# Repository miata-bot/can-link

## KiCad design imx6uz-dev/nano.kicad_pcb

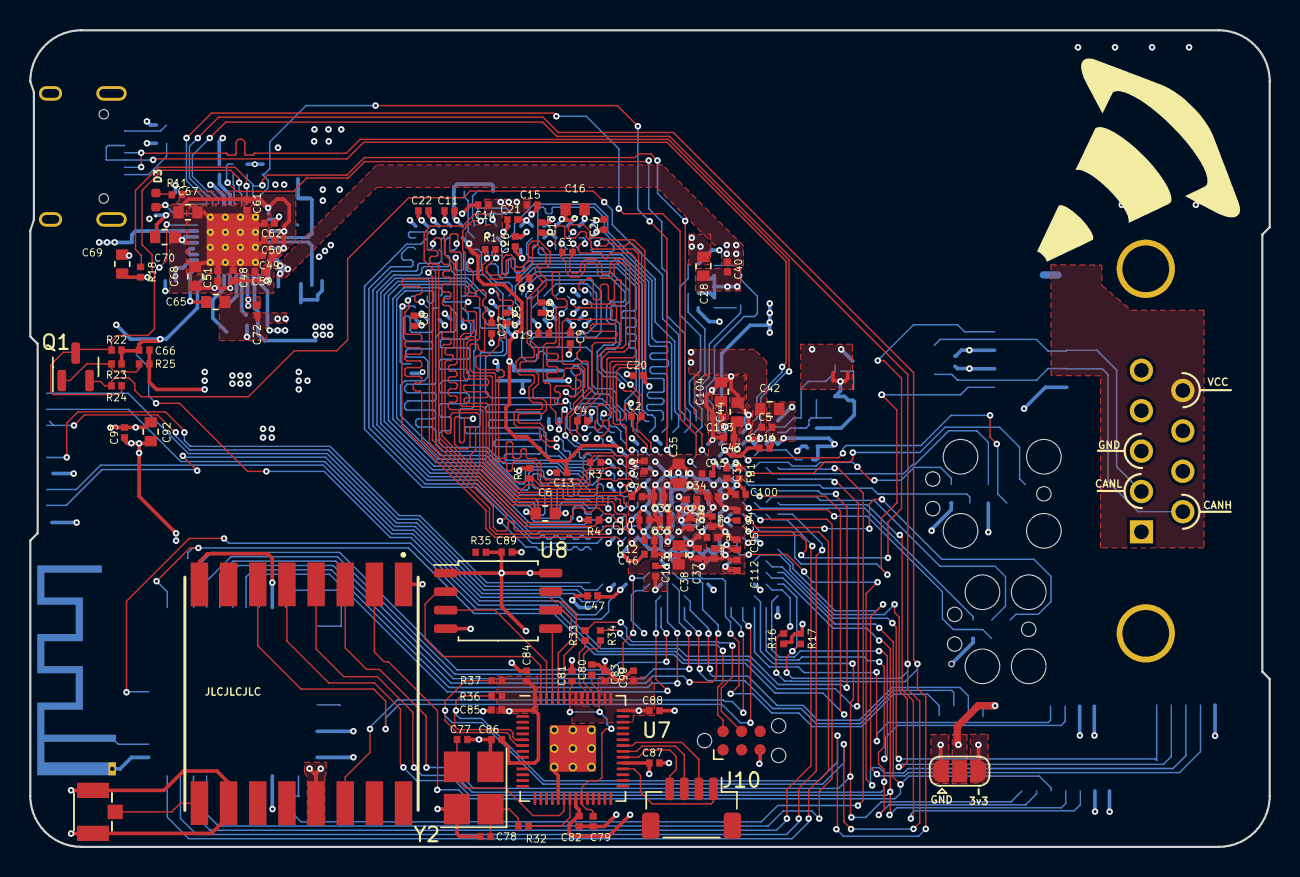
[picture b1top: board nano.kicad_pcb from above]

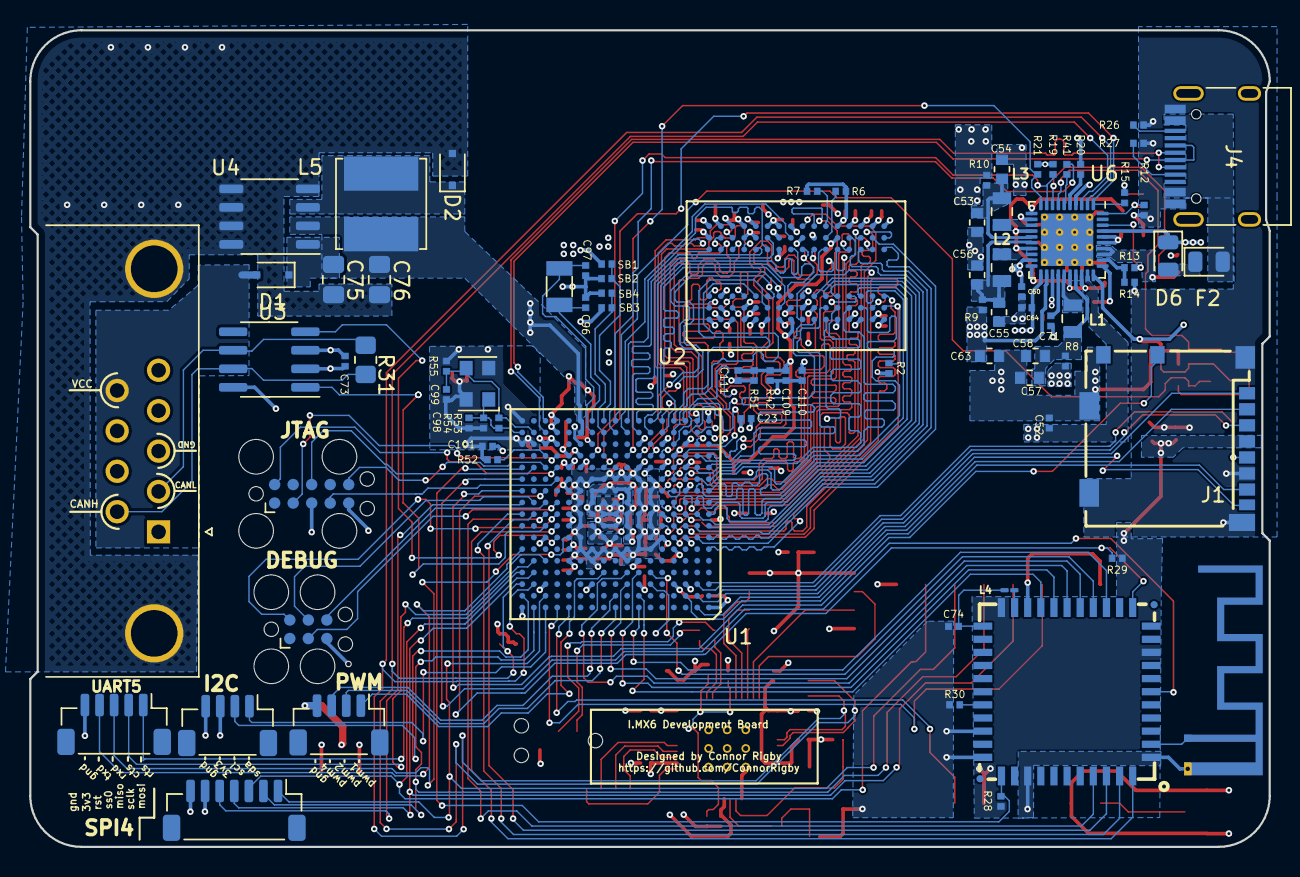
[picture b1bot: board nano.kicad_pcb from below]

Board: 4 copper layers, 85.0 x 56.0 mm, 195 parts (81 on the bottom side), 188 nets.

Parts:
AE1: U.FL-R-SMT-1(10); HRS_U.FL-R-SMT-1(10)
ANT1: PCB_ANTENNA; Texas_SWRA117D_2.4GHz_Left
C1, C2, C3, C4: 2.2pF; C_0402_narrow
C5, C7, C8, C9, C10, C11, C12, C13, C14, C15, C17, C18, C19, C20, C21, C22, C23, C24, C25, C26, C27, C30, C31, C32, C33, C34, C36, C37, C40, C41, C43, C45, C46, C47, C73, C94, C95, C102, C114: 0.22uF; C_0402_narrow
C6, C42, C44, C53, C54, C55, C56, C57, C58, C104: 10uF; C_0603_narrow
C16, C28, C35, C38, C92: 22uF; C_0603_narrow
C29, C39, C48, C49, C50, C52, C60, C62, C110: 4.7uF; C_0402_narrow
C51, C59, C61, C64, C71, C72, C79, C81, C89, C101: 1uF; C_0402_narrow
C63: 1uF; C_0603_narrow
C65: 0.1uF; C_0603_narrow
C66: 0.47uF; C_0402_narrow
C67, C68: 100uF; C_0603_narrow
C69, C70: 4.7uF; C_0603_narrow
C74: 4.7F; C_0402_narrow
C75, C76: 10uF; C_0805_2012Metric_Pad1.18x1.45mm_HandSolder
C77, C78: 10pF; C_0402_narrow
C80, C82, C83, C84, C85, C86, C87, C88, C90, C93, C100, C103, C109, C111, C112, C113: 0.1uF; C_0402_narrow
C96, C97, C98, C99: 18pF; C_0402_narrow
D1, D2: D_Small; D_SOD-323F
D3: LED; LED_0402_1005Metric
D6: D_Schottky; D_0805_2012Metric
F2: Polyfuse; D_0805_2012Metric
FB1: Bead; R_0402_narrow
J1: SD-104031; uSD_104031
J2: TAG_CONNECT_JTAG; Tag-Connect_TC2050-IDC-FP_2x05_P1.27mm_Vertical
J3: TC2030-IDC; Tag-Connect_TC2030-IDC-FP_2x03_P1.27mm_Vertical
J4: USB_C_Receptacle_USB2.0; USB_C_Receptacle_HRO_TYPE-C-31-M-12
J5: CAN; DSUB-9_Female_Horizontal_P2.77x2.84mm_EdgePinOffset4.94mm_H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
J6: UART5; JST_SH_BM05B-SRSS-TB_1x05-1MP_P1.00mm_Vertical
J7: I2C4; JST_SH_BM04B-SRSS-TB_1x04-1MP_P1.00mm_Vertical
J8: ECSPI4; JST_SH_BM07B-SRSS-TB_1x07-1MP_P1.00mm_Vertical
J9: PWM; JST_SH_BM04B-SRSS-TB_1x04-1MP_P1.00mm_Vertical
J10: TC2030-IDC; Tag-Connect_TC2030-IDC-NL_2x03_P1.27mm_Vertical
J11: Conn_01x05; JST_SH_BM04B-SRSS-TB_1x04-1MP_P1.00mm_Vertical
JP1: IO_SW; SolderJumper-3_P1.3mm_Open_RoundedPad1.0x1.5mm
L1, L2, L3: 1uH; L_0805_narrow
L4: 3.3uH; L_01005_0402Metric_Pad0.57x0.30mm_HandSolder
L5: 6.8uH; L_Bourns_SRN6045TA
MOD1: RTL8723BS; RL-SM02BD(RTL8723BS)
Q1: 2SK3018; SOT-23
R1: 470; R_0402_narrow
R2, R4, R5: 10K; R_0402_narrow
R3, R6, R7: 240; R_0402_narrow
R8, R9, R10: 0.02; R_0402_narrow
R11: 47; R_0402_narrow
R12, R14, R24: DNP; R_0402_narrow
R13, R16, R17, R52: 4.7K; R_0402_narrow
R15, R18, R19, R21, R22, R23, R25: 100K; R_0402_narrow
R20, R41: 0R; R_0402_narrow
R26, R27: 5.1k; R_0402_narrow
R28, R29, R32, R35, R36, R37: 1k; R_0402_narrow
R30: 7.13; R_0402_narrow
R31: 120; R_0805_2012Metric_Pad1.20x1.40mm_HandSolder
R33, R34: 27.4; R_0402_narrow
R42, R51: 1.5K; R_0402_narrow
R53: 1M; R_0402_narrow
R54: 499; R_0402_narrow
R55: 2.2M; R_0402_narrow
SB1, SB2, SB3, SB4: 4.7K; R_0402_narrow
U1: IMX6UL_BGA289
U2: DDR3_BGA96
U3: TJA1051T; SOIC-8_3.9x4.9mm_P1.27mm
U4: AP1509; SOP-8_3.9x4.9mm_P1.27mm
U5: RFM69HCW; XCVR_RFM69HW
U6: PF1550; QFN-40-1EP_5x5mm_P0.4mm_EP3.6x3.6mm_ThermalVias
U7: RP2040; RP2040-QFN-56
U8: W25Q128JVS; SOIC-8_5.23x5.23mm_P1.27mm
XTAL2: 24MHz 50ppm; Oscillator_SMD_EuroQuartz_XO32-4Pin_3.2x2.5mm
Y1: 32.768 kHz; Crystal_SMD_3215-2Pin_3.2x1.5mm
Y2: 12mhz; Crystal_SMD_3225-4Pin_3.2x2.5mm_HandSoldering

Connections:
5V: C76.1, D6.1 (K), L5.2, U1.T12 (USB_OTG1_VBUS), U1.U12 (USB_OTG2_VBUS), U4.2 (VOUT), U6.37 (VBUSIN(VIN))
/Clock_and_Control/BOOT0: SB3.1, SB4.1, U1.T10 (BOOT_MODE0)
/Clock_and_Control/BOOT1: SB1.1, SB2.1, U1.U10 (BOOT_MODE1)
/Clock_and_Control/IMX_XTALI: C99.1, R53.1, R55.1, U1.T16 (XTALI), XTAL2.3
/Clock_and_Control/IMX_XTALO: C98.1, R53.2, R54.1, U1.T17 (XTALO), XTAL2.1
/Clock_and_Control/JTAG_MOD: R52.2, U1.P15 (JTAG_MOD)
/Clock_and_Control/JTAG_TCK: J2.4 (SWDCLK/TCK), U1.M14 (JTAG_TCK)
/Clock_and_Control/JTAG_TDI: J2.8 (NC/TDI), U1.N16 (JTAG_TDI)
/Clock_and_Control/JTAG_TDO: J2.6 (SWO/TDO), U1.N15 (JTAG_TDO)
/Clock_and_Control/JTAG_TMS: J2.2 (SWDIO/TMS), U1.P14 (JTAG_TMS)
/Clock_and_Control/JTAG_TRST_B: J2.10 (~RESET), U1.N14 (JTAG_TRST_B)
/Clock_and_Control/RTC_XTALI: C97.1, U1.T11 (RTC_XTALI), Y1.2
/Clock_and_Control/RTC_XTALO: C96.1, U1.U11 (RTC_XTALO), Y1.1
/Clock_and_Control/VDDA_ADC: C100.1, C101.1, FB1.2, U1.L13 (VDDA_ADC_3P3), U1.M13 (ADC_VREFH)
/DDR/A0: U1.L5 (DRAM_ADDR00), U2.N3 (A0)
/DDR/A1: U1.H2 (DRAM_ADDR01), U2.P7 (A1)
/DDR/A2: U1.K1 (DRAM_ADDR02), U2.P3 (A2)
/DDR/A3: U1.M2 (DRAM_ADDR03), U2.N2 (A3)
/DDR/A4: U1.K4 (DRAM_ADDR04), U2.P8 (A4)
/DDR/A5: U1.L1 (DRAM_ADDR05), U2.P2 (A5)
/DDR/A6: U1.G2 (DRAM_ADDR06), U2.R8 (A6)
/DDR/A7: U1.H4 (DRAM_ADDR07), U2.R2 (A7)
/DDR/A8: U1.J4 (DRAM_ADDR08), U2.T8 (A8)
/DDR/A9: U1.L2 (DRAM_ADDR09), U2.R3 (A9)
/DDR/A10: U1.M4 (DRAM_ADDR10), U2.L7 (A10_AP)
/DDR/A11: U1.K3 (DRAM_ADDR11), U2.R7 (A11)
/DDR/A12: U1.L4 (DRAM_ADDR12), U2.N7 (A12_BC#)
/DDR/A13: U1.H3 (DRAM_ADDR13), U2.T3 (A13)
/DDR/A14: U1.G1 (DRAM_ADDR14), U2.T7 (A14)
/DDR/A15: U1.K5 (DRAM_ADDR15), U2.M7 (A15)
/DDR/BA0: U1.M1 (DRAM_SDBA0), U2.M2 (BA0)
/DDR/BA1: U1.H1 (DRAM_SDBA1), U2.N8 (BA1)
/DDR/BA2: U1.K2 (DRAM_SDBA2), U2.M3 (BA2)
/DDR/CAS#: U1.J2 (DRAM_CAS_B), U2.K3 (CAS#)
/DDR/CK+: R1.2, U1.P1 (DRAM_SDCLK0_P), U2.J7 (CK)
/DDR/CK-: R1.1, U1.P2 (DRAM_SDCLK0_N), U2.K7 (CK#)
/DDR/CKE0: R5.1, U1.M3 (DRAM_SDCKE0), U2.K9 (CKE)
/DDR/CKE1: R4.1, U1.J3 (DRAM_SDCKE1), U2.J9 (CKE1)
/DDR/CS0#: U1.N2 (DRAM_CS0_B), U2.L2 (CS#)
/DDR/CS1#: U1.H5 (DRAM_CS1_B), U2.L1 (CS1)
/DDR/DML: U1.T7 (DRAM_DQM0), U2.E7 (DML)
/DDR/DMU: U1.T3 (DRAM_DQM1), U2.D3 (DMU)
/DDR/DQL0: U1.T4 (DRAM_DATA00), U2.E3 (DQL0)
/DDR/DQL1: U1.U6 (DRAM_DATA01), U2.H3 (DQL4)
/DDR/DQL2: U1.T6 (DRAM_DATA02), U2.H7 (DQL7)
/DDR/DQL3: U1.U7 (DRAM_DATA03), U2.F8 (DQL3)
/DDR/DQL4: U1.U8 (DRAM_DATA04), U2.F7 (DQL1)
/DDR/DQL5: U1.T8 (DRAM_DATA05), U2.H8 (DQL5)
/DDR/DQL6: U1.T5 (DRAM_DATA06), U2.G2 (DQL6)
/DDR/DQL7: U1.U4 (DRAM_DATA07), U2.F2 (DQL2)
/DDR/DQSL+: C1.1, C2.1, U1.P6 (DRAM_SDQS0_P), U2.F3 (DQSL)
/DDR/DQSL-: C1.2, C2.2, U1.P7 (DRAM_SDQS0_N), U2.G3 (DQSL#)
/DDR/DQSU+: C3.1, C4.1, U1.T1 (DRAM_SDQS1_P), U2.C7 (DQSU)
/DDR/DQSU-: C3.2, C4.2, U1.T2 (DRAM_SDQS1_N), U2.B7 (DQSU#)
/DDR/DQU0: U1.U2 (DRAM_DATA08), U2.D7 (DQU0)
/DDR/DQU1: U1.U3 (DRAM_DATA09), U2.C3 (DQU1)
/DDR/DQU2: U1.U5 (DRAM_DATA10), U2.C8 (DQU2)
/DDR/DQU3: U1.R4 (DRAM_DATA11), U2.C2 (DQU3)
/DDR/DQU4: U1.P5 (DRAM_DATA12), U2.A7 (DQU4)
/DDR/DQU5: U1.P3 (DRAM_DATA13), U2.A2 (DQU5)
/DDR/DQU6: U1.R2 (DRAM_DATA14), U2.B8 (DQU6)
/DDR/DQU7: U1.R1 (DRAM_DATA15), U2.A3 (DQU7)
/DDR/ODT0: U1.N1 (DRAM_ODT0), U2.K1 (ODT)
/DDR/ODT1: U1.F1 (DRAM_ODT1), U2.J1 (ODT1)
/DDR/RAS#: U1.M5 (DRAM_RAS_B), U2.J3 (RAS#)
/DDR/RESET#: R2.1, U1.G4 (DRAM_RESET), U2.T2 (RESET#)
/DDR/WE#: U1.J1 (DRAM_SDWE_B), U2.L3 (WE#)
/DDR/ZQ: R6.2, U2.L8 (ZQ)
/DDR/ZQ1: R7.2, U2.L9 (ZQ1)
/DDR/ZQPAD: R3.2, U1.N4 (DRAM_ZQPAD)
/IMX_Peripherals_1/TOUCH_MISO: J8.3, U1.D17 (ENET2_TX_CLK), U5.2 (MISO)
/IMX_Peripherals_1/TOUCH_MOSI: J8.1, U1.B15 (ENET2_TX_EN), U5.3 (MOSI)
/IMX_Peripherals_1/TOUCH_SCL: J7.2, U1.B17 (ENET2_RX_EN)
/IMX_Peripherals_1/TOUCH_SCLK: J8.2, U1.A16 (ENET2_TX_DATA1), U5.4 (SCK)
/IMX_Peripherals_1/TOUCH_SDA: J7.1, U1.A15 (ENET2_TX_DATA0)
/IMX_Peripherals_1/TOUCH_SS0: J8.4, U1.D16 (ENET2_RX_ER), U5.5 (NSS)
/IMX_Peripherals_2/CC1: J4.A5 (CC1), R27.1
/IMX_Peripherals_2/CC2: J4.B5 (CC2), R26.1
/IMX_Peripherals_2/LCD_D0: J9.3, U1.B9 (LCD_DATA00)
/IMX_Peripherals_2/LCD_D1: J9.2, U1.A9 (LCD_DATA01)
/IMX_Peripherals_2/LCD_D3: J9.1, U1.D10 (LCD_DATA03)
/IMX_Peripherals_2/VDDUSB_CAP: C103.1, C104.1, U1.R12 (VDD_USB_CAP)
/IMX_Power_Pins/VDD_SNVS_CAP: C45.1, U1.N12 (VDD_SNVS_CAP)
/PMIC PF1550/BUCK_VIN: C75.1, D1.1 (K), U4.1 (VIN)
/PMIC PF1550/CHGB: D3.1 (K), R12.1, U6.40 ((GND)CHGB)
/PMIC PF1550/ON_KEY: R18.1, U6.8 (ONKEY)
/PMIC PF1550/POWERON: R41.1, U6.6 (POWERON)
/PMIC PF1550/STANDBY: Q1.3 (D), R22.2, R24.1, U6.7 (STANDBY)
/PMIC PF1550/SW1LX: L1.2, U6.25 (SW1LX)
/PMIC PF1550/SW1OUT: C57.1, C58.1, L1.1, R8.1, U6.27 (SW1FB)
/PMIC PF1550/SW2LX: L2.2, U6.18 (SW2LX)
/PMIC PF1550/SW2OUT: C55.1, C56.1, L2.1, R9.1, U6.16 (SW2FB)
/PMIC PF1550/SW3LX: L3.2, U6.13 (SW3LX)
/PMIC PF1550/SW3OUT: C53.1, C54.1, L3.1, R10.1, U6.15 (SW3FB)
/PMIC PF1550/VCORE: C71.1, U6.24 (VCORE)
/PMIC PF1550/VDDOTP: R20.2, U6.5 (VDDOTP)
/PMIC PF1550/VDIG: C72.1, U6.23 (VDIG)
/WIFI_BT/SDIO_VSEL: MOD1.29, R30.2
/WIFI_BT/VIN_LDO: C74.1, L4.2, MOD1.23
/WIFI_BT/VIN_LDO_OUT: L4.1, MOD1.21
/rp2040/1v1: C79.1, C80.1, C81.1, U7.23 (DVDD), U7.45 (VREG_VOUT), U7.50 (DVDD)
/rp2040/PICO_USB_DM: J10.2 (SWDIO), R34.1
/rp2040/PICO_USB_DP: J10.4 (SWCLK), R33.2
/rp2040/QSPI_SCLK: U7.52 (QSPI_SCLK), U8.6 (CLK)
/rp2040/QSPI_SD0: U7.53 (QSPI_SD0), U8.5 (DI(IO0))
/rp2040/QSPI_SD1: U7.55 (QSPI_SD1), U8.2 (DO(IO1))
/rp2040/QSPI_SD2: U7.54 (QSPI_SD2), U8.3 (IO2)
/rp2040/QSPI_SD3: U7.51 (QSPI_SD3), U8.7 (IO3)
BATT_THM: R13.1, R14.2, U6.32 (THM(GND))
BOARD_SCL: R17.2, R37.1, U1.C17 (ENET2_RX_DATA0), U6.3 (SCL), U7.7 (GPIO5)
BOARD_SDA: R16.2, R36.1, U1.C16 (ENET2_RX_DATA1), U6.2 (SDA), U7.6 (GPIO4)
BT_RST: MOD1.34, R28.2, U1.N17 (GPIO1_IO08)
BT_WAKE: MOD1.6, U1.M17 (GPIO1_IO05)
CAN_H: J5.6, R31.1, U3.7 (CANH)
CAN_L: J5.2, R31.2, U3.6 (CANL)
DBG_CTS: J3.2, U1.J14 (UART1_RTS_B)
DBG_GPIO0: MOD1.12, R29.2, U1.L15 (GPIO1_IO01)
DBG_RTS: J3.6, U1.K15 (UART1_CTS_B)
DBG_RXD: J3.3, U1.K14 (UART1_TX_DATA)
DBG_TXD: J3.4, U1.K16 (UART1_RX_DATA)
DCDC_3V3: C73.1, C82.1, C83.2, C84.1, C85.1, C86.1, C87.1, C88.1, C89.1, C90.1, C92.1, C93.1, C94.1, C95.1, C102.1, C112.1, C113.1, J1.4 (VDD), J7.3, J8.6, JP1.3 (B), MOD1.9, MOD1.22, R10.2, R15.1, R16.1, R17.1, R28.1, R29.1, R35.2, R36.2, R37.2, U1.E7 (NVCC_NAND), U1.E13 (NVCC_LCD), U1.F13 (NVCC_ENET), U1.H13 (NVCC_UART), U1.J13 (NVCC_GPIO), U3.3 (VCC), U5.13 (3.3V), U6.4 (VDDIO), U7.1 (IOVDD), U7.10 (IOVDD), U7.22 (IOVDD), U7.33 (IOVDD), U7.42 (IOVDD), U7.43 (ADC_AVDD), U7.44 (VREG_IN), U7.48 (USB_VDD), U7.49 (IOVDD), U7.56 (QSPI_SS), U8.1 (~CS), U8.8 (VCC)
DRAM_1V35: C6.1, C7.1, C8.1, C9.1, C10.1, C11.1, C12.1, C16.1, C17.1, C18.1, C19.1, C20.1, C21.1, C22.1, C23.1, C24.1, C25.1, C26.1, C27.1, C63.1, C109.1, C110.1, R9.2, R42.2, U1.G6 (NVCC_DRAM), U1.H6 (NVCC_DRAM), U1.J6 (NVCC_DRAM), U1.K6 (NVCC_DRAM), U1.L6 (NVCC_DRAM), U1.M6 (NVCC_DRAM), U2.A1 (VDDQ), U2.A8 (VDDQ), U2.B2 (VDD), U2.C1 (VDDQ), U2.C9 (VDDQ), U2.D2 (VDDQ), U2.D9 (VDD), U2.E9 (VDDQ), U2.F1 (VDDQ), U2.G7 (VDD), U2.H2 (VDDQ), U2.H9 (VDDQ), U2.K2 (VDD), U2.K8 (VDD), U2.N1 (VDD), U2.N9 (VDD), U2.R1 (VDD), U2.R9 (VDD), U6.22 (VINREFDDR)
ETH_MDIO: J8.5, U1.K17 (GPIO1_IO06)
ETH_RXEN: J6.1, U1.E16 (ENET1_RX_EN)
ETH_TXD0: J6.2, U1.E15 (ENET1_TX_DATA0)
FLEXCAN1_RX: U1.G14 (UART3_RTS_B), U3.4 (RXD)
FLEXCAN1_TX: U1.H15 (UART3_CTS_B), U3.1 (TXD)
GND: AE1.1, AE1.3, ANT1.2 (Shield), C5.2, C6.2, C7.2, C8.2, C9.2, C10.2, C11.2, C12.2, C13.2, C14.2, C15.2, C16.2, C17.2, C18.2, C19.2, C20.2, C21.2, C22.2, C23.2, C24.2, C25.2, C26.2, C27.2, C28.2, C29.2, C30.2, C31.2, C32.2, C33.2, C34.2, C35.2, C36.2, C37.2, C38.2, C39.2, C40.2, C41.2, C42.2, C43.2, C44.2, C45.2, C46.2, C47.2, C48.2, C49.2, C50.2, C51.2, C52.2, C53.2, C54.2, C55.2, C56.2, C57.2, C58.2, C59.2, C60.2, C61.2, C62.2, C63.2, C64.2, C65.2, C66.2, C67.2, C68.2, C69.2, C70.2, C71.2, C72.2, C73.2, C74.2, C75.2, C76.2, C77.2, C78.2, C79.2, C80.2, C81.2, C82.2, C83.1, C84.2, C85.2, C86.2, C87.2, C88.2, C89.2, C90.2, C92.2, C93.2, C94.2, C95.2, C96.2, C97.2, C98.2, C99.2, C100.2, C101.2, C102.2, C103.2, C104.2, C110.2, C111.2, C112.2, C113.2, C114.2, D2.2 (A), J1.6 (GND), J1.10 (SW2), J1.11 (Shield1), J1.12 (Shield2), J1.13 (Shield3), J1.14 (Shield4), J2.3 (GND), J2.5 (GND), J3.5, J4.A1 (GND), J4.A12 (GND), J4.B1 (GND), J4.B12 (GND), J5.0 (PAD), J5.3, J6.5, J7.4, J8.7, J10.5 (GND), JP1.1 (A), MOD1.1, MOD1.20, MOD1.31, MOD1.33, MOD1.36, R2.2, R3.1, R4.2, R5.2, R6.1, R7.1, R12.2, R14.1, R20.1, R25.1, R26.2, R27.2, R30.1, R51.1, R52.1, R54.2, R55.2, SB2.2, SB4.2, U1.A1 (VSS), U1.A17 (VSS), U1.C3 (VSS), U1.C7 (VSS), U1.C11 (VSS), U1.C15 (VSS), U1.E8 (VSS), U1.E11 (VSS), U1.F6 (VSS), U1.F7 (VSS), U1.F8 (VSS), U1.F9 (VSS), U1.F10 (VSS), U1.F11 (VSS), U1.F12 (VSS), U1.G3 (VSS), U1.G5 (VSS), U1.G7 (VSS), U1.G12 (VSS), U1.G15 (VSS), U1.H7 (VSS), U1.H12 (VSS), U1.J5 (VSS), U1.J7 (VSS), U1.J12 (VSS), U1.K7 (VSS), U1.K12 (VSS), U1.L3 (VSS), U1.L7 (VSS), U1.L12 (VSS), U1.M7 (VSS), U1.M8 (VSS), U1.M9 (VSS), U1.M10 (VSS), U1.M11 (VSS), U1.M12 (NGND_KEL0), U1.N3 (VSS), U1.N5 (VSS), U1.N7 (TEST_MODE), U1.R3 (VSS), U1.R5 (VSS), U1.R7 (VSS), U1.R11 (VSS), U1.R16 (VSS), U1.R17 (VSS), U1.T14 (VSS), U1.U1 (VSS), U1.U14 (VSS), U1.U17 (VSS), U2.A9 (VSS), U2.B1 (VSSQ), U2.B3 (VSS), U2.B9 (VSSQ), U2.D1 (VSSQ), U2.D8 (VSSQ), U2.E1 (VSS), U2.E2 (VSSQ), U2.E8 (VSSQ), U2.F9 (VSSQ), U2.G1 (VSSQ), U2.G8 (VSS), U2.G9 (VSSQ), U2.J2 (VSS), U2.J8 (VSS), U2.M1 (VSS), U2.M9 (VSS), U2.P1 (VSS), U2.P9 (VSS), U2.T1 (VSS), U2.T9 (VSS), U3.2 (GND), U3.8 (S), U4.4 (SD), U4.5 (GND5), U4.6 (GND6), U4.7 (GND7), U4.8 (GND8), U5.1 (GND), U5.8 (GND), U5.10 (GND), U6.41 (EP), U7.19 (TESTEN), U7.57 (GND), U8.4 (GND), XTAL2.2, XTAL2.4, Y2.2, Y2.4
LICELL: C65.1, U6.31 (LICELL)
NVCC_CSI: C46.1, C52.1, U1.F4 (NVCC_CSI), U6.29 (VLDO1)
NVCC_PLL_OUT: C43.1, C44.1, U1.P13 (NVCC_PLL)
NVCC_SD: C47.1, C62.1, U1.C4 (NVCC_SD1), U6.12 (VLDO3)
unnamed: AE1.2, U5.9 (ANT)
unnamed: ANT1.1 (A), MOD1.2
unnamed: C77.1, U7.20 (XIN), Y2.3
unnamed: C78.1, R32.2, Y2.1
unnamed: D2.1 (K), L5.1, U4.3 (FB)
unnamed: D3.2 (A), R11.1
unnamed: D6.2 (A), F2.1
unnamed: J9.4, JP1.2 (C)
unnamed: J11.1, U7.32 (GPIO21)
unnamed: J11.2, U7.36 (GPIO24)
unnamed: J11.3, U7.35 (GPIO23)
unnamed: J11.4, U7.34 (GPIO22)
unnamed: Q1.1 (G), R23.2, R25.2
unnamed: R13.2, U6.38 (INT2P7(LDO2P7))
unnamed: R32.1, U7.21 (XOUT)
unnamed: R33.1, U7.47 (USB_DP)
unnamed: R34.2, U7.46 (USB_DM)
OTG_D+: J4.A6 (D+), J4.B6 (D+), U1.U15 (USB_OTG1_DP)
OTG_D-: J4.A7 (D-), J4.B7 (D-), U1.T15 (USB_OTG1_DN)
OTG_VBUS: F2.2, J4.A4 (VBUS), J4.A9 (VBUS), J4.B4 (VBUS), J4.B9 (VBUS)
PMIC_INT: R19.1, U1.P11 (SNVS_TAMPER2), U6.9 (INTB)
PMIC_ON_REQ: R41.2, U1.T9 (SNVS_PMIC_ON_REQ)
PMIC_STBY_REQ: Q1.2 (S), R24.2, U1.U9 (CCM_PMIC_STBY_REQ)
PMIC_WDI: R15.2, U1.N10 (SNVS_TAMPER7), U6.1 (WDI)
POR_B: R21.1, U1.P8 (POR_B), U6.10 (RESETBMCU)
RF69_INT: U1.A13 (LCD_DATA18), U5.14 (DIO0)
RF69_RESET: U1.A14 (LCD_DATA22), U5.6 (RESET)
SD1_CD_B: J1.9 (SW1), U1.L17 (GPIO1_IO03)
SD1_CLK: J1.5 (CLK), U1.C1 (SD1_CLK)
SD1_CMD: J1.3 (CMD), U1.C2 (SD1_CMD)
SD1_D0: J1.7 (D0), U1.B3 (SD1_DATA0)
SD1_D1: J1.8 (D1), U1.B2 (SD1_DATA1)
SD1_D2: J1.1 (D2), U1.B1 (SD1_DATA2)
SD1_D3: J1.2 (D3), U1.A2 (SD1_DATA3)
SDHC_CLK: MOD1.17, U1.D8 (NAND_RE_B)
SDHC_CMD: MOD1.16, U1.C8 (NAND_WE_B)
SDHC_DATA0: MOD1.18, U1.D7 (NAND_DATA00)
SDHC_DATA1: MOD1.19, U1.B7 (NAND_DATA01)
SDHC_DATA2: MOD1.14, U1.A7 (NAND_DATA02)
SDHC_DATA3: MOD1.15, U1.D6 (NAND_DATA03)
UART2_CTS: MOD1.41, U1.J15 (UART2_CTS_B)
UART2_RTS: MOD1.44, U1.H14 (UART2_RTS_B)
UART2_RXD: MOD1.42, U1.J16 (UART2_RX_DATA)
UART2_TXD: MOD1.43, U1.J17 (UART2_TX_DATA)
UART_5_RXD: J6.3, U1.G13 (UART5_RX_DATA)
UART_5_TXD: J6.4, U1.F17 (UART5_TX_DATA)
VBATT: C69.1, R18.2, U6.33 ((NC)VBATT1), U6.34 ((NC)VBATT2)
VCC: D1.2 (A), J5.9
VDD_ARM_CAP: C36.1, C37.1, C38.1, U1.G9 (VDD_ARM_CAP), U1.G10 (VDD_ARM_CAP), U1.G11 (VDD_ARM_CAP), U1.H11 (VDD_ARM_CAP)
VDD_HIGH_CAP: C5.1, C41.1, C42.1, U1.N6 (NVCC_DRAM_2P5), U1.R14 (VDD_HIGH_CAP), U1.R15 (VDD_HIGH_CAP)
VDD_HIGH_IN: C39.1, C40.1, C60.1, FB1.1, U1.N13 (VDD_HIGH_IN), U6.19 (VLDO2)
VDD_SNVS: C66.1, C114.1, R19.2, R21.2, R22.1, R23.1, SB1.2, SB3.2, U1.P12 (VDD_SNVS_IN), U6.30 (VSNVS)
VDD_SOC_CAP: C32.1, C33.1, C34.1, C35.1, U1.G8 (VDD_SOC_CAP), U1.H8 (VDD_SOC_CAP), U1.J8 (VDD_SOC_CAP), U1.J11 (VDD_SOC_CAP), U1.K8 (VDD_SOC_CAP), U1.K11 (VDD_SOC_CAP), U1.L8 (VDD_SOC_CAP), U1.L9 (VDD_SOC_CAP), U1.L10 (VDD_SOC_CAP), U1.L11 (VDD_SOC_CAP)
VDD_SOC_IN: C28.1, C29.1, C30.1, C31.1, R8.2, U1.H9 (VDD_SOC_IN), U1.H10 (VDD_SOC_IN), U1.J9 (VDD_SOC_IN), U1.J10 (VDD_SOC_IN), U1.K9 (VDD_SOC_IN), U1.K10 (VDD_SOC_IN)
VREFDDR: C13.1, C14.1, C15.1, C64.1, C109.2, C111.1, R42.1, R51.2, U1.P4 (DRAM_VREF), U2.H1 (VREFDQ), U2.M8 (VREFCA), U6.21 (VREFDDR)
VSYS: C48.1, C49.1, C50.1, C51.1, C59.1, C61.1, C67.1, C68.1, C70.1, R11.2, U6.11 (VLDO3IN), U6.14 (SW3IN), U6.17 (SW2IN), U6.20 (VLDO2IN), U6.26 (SW1IN), U6.28 (VLDO1IN), U6.35 (VSYS1), U6.36 (VSYS2)
